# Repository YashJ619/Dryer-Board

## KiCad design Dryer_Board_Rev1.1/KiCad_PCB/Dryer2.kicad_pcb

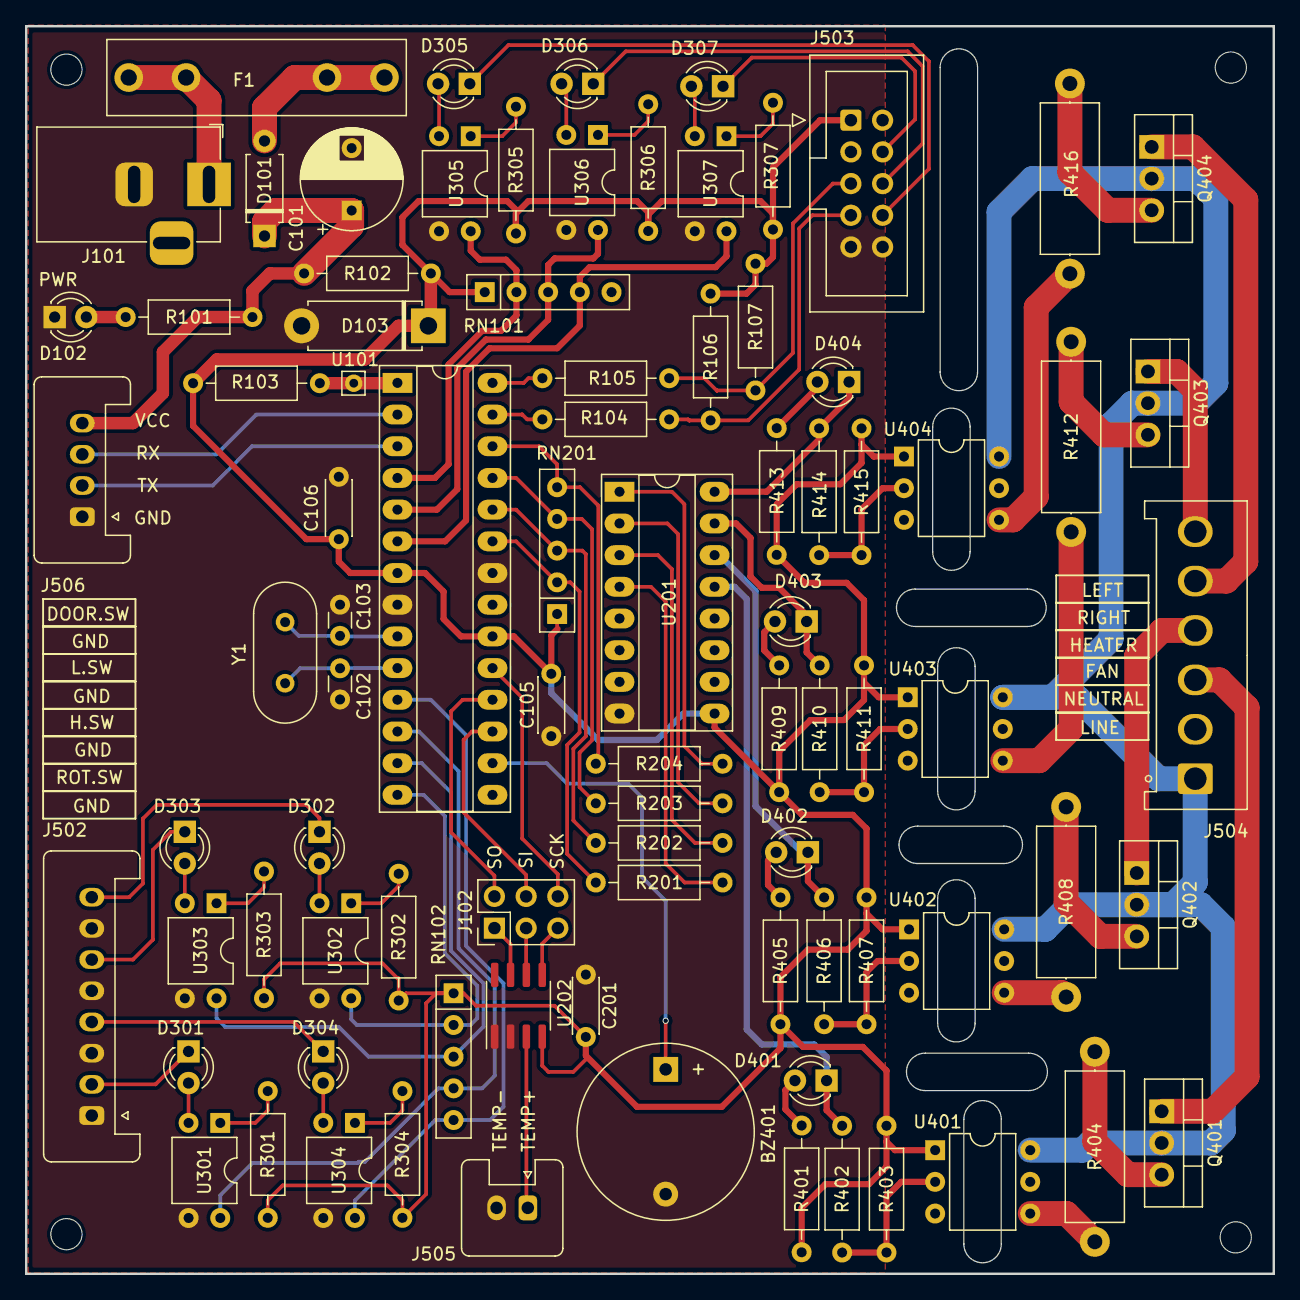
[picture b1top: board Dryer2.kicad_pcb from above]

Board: 2 copper layers, 100.0 x 100.0 mm, 89 parts (0 on the bottom side), 84 nets.

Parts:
BZ401: Buzzer; Buzzer_D14mm_H7mm_P10mm
C101: 220uF16v; CP_Radial_D8.0mm_P5.00mm
C102, C103: 22p; C_Disc_D3.0mm_W1.6mm_P2.50mm
C105, C106, C201: 100n; C_Disc_D4.3mm_W1.9mm_P5.00mm
D101: 1N5819; D_A-405_P7.62mm_Horizontal
D102, D301, D302, D303, D304, D305, D306, D307, D401, D402, D403, D404: LED; LED_D3.0mm
D103: 5.1v; D_5W_P10.16mm_Horizontal
F1: 1A; Fuseholder_Littelfuse_100_series_5x20mm
H501: 2.5MM; MountingHole_2.5mm
H502, H503, H504: MountingHole; MountingHole_2.5mm
J101: DC_Jack; BarrelJack_Horizontal
J102: MAX_AVR_SPI; PinHeader_2x03_P2.54mm_Vertical
J502: INPUT; Stocko_MKS_1658-6-0-808_1x8_P2.50mm_Vertical
J503: PANEL; IDC-Header_2x05_P2.54mm_Vertical
J504: MOTOR; Hirose_DF63-6P-3.96DSA_1x06_P3.96mm_Vertical
J505: Thermocupler; Stocko_MKS_1652-6-0-202_1x2_P2.50mm_Vertical
J506: UART; Stocko_MKS_1654-6-0-404_1x4_P2.50mm_Vertical
Q401, Q402, Q403, Q404: BTA16-800B; TO-220-3_Vertical
R101, R103, R201, R202, R203, R204, R401, R403, R405, R407, R409, R411, R413, R415: 1k; R_Axial_DIN0207_L6.3mm_D2.5mm_P10.16mm_Horizontal
R102: 4R7; R_Axial_DIN0207_L6.3mm_D2.5mm_P10.16mm_Horizontal
R104, R105: 22R; R_Axial_DIN0207_L6.3mm_D2.5mm_P10.16mm_Horizontal
R106, R107: 10K; R_Axial_DIN0207_L6.3mm_D2.5mm_P10.16mm_Horizontal
R301, R302, R303, R304, R305, R306, R307: 470R; R_Axial_DIN0207_L6.3mm_D2.5mm_P10.16mm_Horizontal
R402, R406, R410, R414: 150R; R_Axial_DIN0207_L6.3mm_D2.5mm_P10.16mm_Horizontal
R404, R408, R412, R416: 1.5K; R_Axial_DIN0414_L11.9mm_D4.5mm_P15.24mm_Horizontal
RN101, RN102, RN201: 10K; R_Array_SIP5
U101: ATmega328P-P; DIP-28_W7.62mm_Socket_LongPads
U201: ULN2003A; DIP-16_W7.62mm_Socket_LongPads
U202: MAX6675; SOIC-8_3.9x4.9mm_P1.27mm
U301, U302, U303, U304, U305, U306, U307: PC817; DIP-4_W7.62mm
U401, U402, U403, U404: MOC3041M; DIP-6_W7.62mm
Y1: 16MHz; Crystal_HC18-U_Vertical

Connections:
#DRUM_LEFT: D401.1 (K), R402.1, U201.13 (O4)
#DRUM_RIGHT: D402.1 (K), R406.1, U201.14 (O3)
#FAN: D404.1 (K), R414.1, U201.16 (O1)
#HEATER: D403.1 (K), R410.1, U201.15 (O2)
#RESET: R103.2, U101.1 (~RESET/PC6)
+5V: C105.1, C106.1, C201.2, D103.1 (K), J503.1, R102.1, R103.1, R106.1, R107.1, R301.1, R302.1, R303.1, R304.1, R305.1, R306.1, R307.1, R401.2, R403.1, R405.2, R407.1, R409.2, R411.1, R413.2, R415.1, RN101.1 (common), RN102.1 (common), RN201.1 (common), U101.7 (VCC), U101.20 (AVCC), U201.9 (COM), U202.4 (VCC), U401.1, U402.1, U403.1, U404.1
/MCU/AVR_SCL: R105.1, U101.28 (PC5)
/MCU/AVR_SDA: R104.1, U101.27 (PC4)
/MCU/XTAL+: C102.2, U101.10 (XTAL2/PB7), Y1.2
/MCU/XTAL-: C103.1, U101.9 (XTAL1/PB6), Y1.1
/ULN2003 MAX6675/D_FAN: R204.2, U201.1 (I1)
/ULN2003 MAX6675/D_HEATER: R203.2, U201.2 (I2)
/ULN2003 MAX6675/D_LEFT: R201.2, U201.4 (I4)
/ULN2003 MAX6675/D_RIGHT: R202.2, U201.3 (I3)
AVR_SCK: J102.6, U101.19 (PB5)
AVR_SI: J102.4, U101.17 (PB3)
AVR_SO: J102.2, U101.18 (PB4)
BUZZER: BZ401.1 (-), U101.16 (PB2)
DOOR_SW: RN102.4 (R3), U101.12 (PD6), U301.4
DOOR_SW_IN: D301.1 (K), J502.2
DRUM_LEFT: R201.1, RN201.2 (R1), U101.23 (PC0)
DRUM_LEFT_LINE: J504.3, Q401.1 (A1)
DRUM_RIGHT: R202.1, RN201.3 (R2), U101.24 (PC1)
DRUM_RIGHT_LINE: J504.4, Q402.1 (A1)
FAN: R204.1, RN201.5 (R4), U101.26 (PC3)
FAN_LINE: J504.5, Q404.1 (A1)
GND: BZ401.2 (+), C101.2, C102.1, C103.2, C105.2, C106.2, C201.1, D102.1 (K), D103.2 (A), J101.2, J502.1, J502.3, J502.5, J502.7, J503.9, J503.10, J505.2, J506.1, U101.8 (GND), U101.22 (AGND), U201.8 (GND), U202.1 (GND), U202.2 (T-), U301.3, U302.3, U303.3, U304.3, U305.3, U306.3, U307.3
HEATER: R203.1, RN201.4 (R3), U101.25 (PC2)
HEATER_LINE: J504.6, Q403.1 (A1)
HEATER_SW: RN102.3 (R2), U101.13 (PD7), U303.4
HEATER_SW_IN: D303.1 (K), J502.6
HIGH_KEY_SW: RN101.4 (R3), U101.6 (PD4), U307.4
HIGH_KEY_SW_IN: D307.1 (K), J503.4
LIMIT_SW: RN102.2 (R1), U101.14 (PB0), U302.4
LIMIT_SW_IN: D302.1 (K), J502.8
LINE_IN: J504.1, Q401.2 (A2), Q402.2 (A2), Q403.2 (A2), Q404.2 (A2), U401.6, U402.6, U403.6, U404.6
LOW_KEY_SW: RN101.2 (R1), U101.4 (PD2), U305.4
LOW_KEY_SW_IN: D305.1 (K), J503.8
MED_KEY_SW: RN101.3 (R2), U101.5 (PD3), U306.4
MED_KEY_SW_IN: D306.1 (K), J503.6
unnamed: D101.2 (A), F1.2
unnamed: D102.2 (A), R101.1
unnamed: D301.2 (A), U301.2
unnamed: D302.2 (A), U302.2
unnamed: D303.2 (A), U303.2
unnamed: D304.2 (A), U304.2
unnamed: D305.2 (A), U305.2
unnamed: D306.2 (A), U306.2
unnamed: D307.2 (A), U307.2
unnamed: D401.2 (A), R401.1
unnamed: D402.2 (A), R405.1
unnamed: D403.2 (A), R409.1
unnamed: D404.2 (A), R413.1
unnamed: F1.1, J101.1
unnamed: Q401.3 (G), R404.2
unnamed: Q402.3 (G), R408.2
unnamed: Q403.3 (G), R412.2
unnamed: Q404.3 (G), R416.2
unnamed: R301.2, U301.1
unnamed: R302.2, U302.1
unnamed: R303.2, U303.1
unnamed: R304.2, U304.1
unnamed: R305.2, U305.1
unnamed: R306.2, U306.1
unnamed: R307.2, U307.1
unnamed: R402.2, R403.2, U401.2
unnamed: R404.1, U401.4
unnamed: R406.2, R407.2, U402.2
unnamed: R408.1, U402.4
unnamed: R410.2, R411.2, U403.2
unnamed: R412.1, U403.4
unnamed: R414.2, R415.2, U404.2
unnamed: R416.1, U404.4
RX: J506.3, U101.2 (PD0)
SCL: J503.5, R105.2, R107.2
SDA: J503.7, R104.2, R106.2
SEL_ROT_SW: RN102.5 (R4), U101.11 (PD5), U304.4
SEL_ROT_SW_IN: D304.1 (K), J502.4
TEMP+: J505.1, U202.3 (T+)
TX: J506.2, U101.3 (PD1)
T_CS: J102.3, U202.6 (~CS)
T_SCK: J102.5, U202.5 (SCK)
T_SO: J102.1, U202.7 (SO)
VCC: C101.1, D101.1 (K), J506.4, R101.2, R102.2

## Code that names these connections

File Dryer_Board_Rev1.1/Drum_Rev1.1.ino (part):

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#include <max6675.h>
#include <LiquidCrystal_I2C.h>

#define DRUM_LEFT_PIN   A0
#define DRUM_RIGHT_PIN  A1
#define FAN_PIN         A2
#define HEATER_PIN      A3

#define SELECT_ROTATION_PIN    8
#define DOOR_PIN               5
#define LIMIT_SW_PIN           6
#define HEATERTEMP_SW_PIN      7

#define LOW_SET_PIN     2
#define MED_SET_PIN     3
#define HIGH_SET_PIN    4

#define BUZZER_PIN      10

#define TEMP_PIN_S0        11
#define TEMP_PIN_CS        12
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void setup() {
  Serial.begin(9600);

  pinMode(DRUM_LEFT_PIN, OUTPUT);
  pinMode(DRUM_RIGHT_PIN, OUTPUT);
  pinMode(FAN_PIN, OUTPUT);
  pinMode(HEATER_PIN, OUTPUT);

  pinMode(BUZZER_PIN, OUTPUT);

  pinMode(DOOR_PIN, INPUT_PULLUP);
  pinMode(HEATERTEMP_SW_PIN, INPUT_PULLUP);
  pinMode(LIMIT_SW_PIN, INPUT_PULLUP);
  pinMode(SELECT_ROTATION_PIN, INPUT_PULLUP);

  pinMode(LOW_SET_PIN, INPUT_PULLUP);
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      if (heatCountdownTime == 0)
      {
        gap = 3;
        digitalWrite(HEATER_PIN, LOW);
      }
    }
    else if (coolCountdownTime > 0)
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    {
      processcomplete = true;
      buzzer = !buzzer;
      digitalWrite(BUZZER_PIN, buzzer);
    }
    else
    {
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    else {
      heatererror = false;
    }
    if (digitalRead(LIMIT_SW_PIN)) {
      limitswerror = true;
    }
    else {
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{
  stopdrum();
  stopbuzzer();
  digitalWrite(FAN_PIN, LOW);
  digitalWrite(HEATER_PIN, LOW);
}

void stopbuzzer()
{
  buzzer = false;
  digitalWrite(BUZZER_PIN, buzzer);
}
void stopdrum()
{
  digitalWrite(DRUM_LEFT_PIN, LOW);
  digitalWrite(DRUM_RIGHT_PIN, LOW);
}

void drumstartwithheater(uint32_t htime)
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    //Serial.println(drumTemp);
    if ((drumTemp < (setTemp - 5)) && (drumTemp > 0))                //Turn heater ON if current temperature is less than (set temperature - 2)
    {
      digitalWrite(HEATER_PIN, HIGH);
    }
    else if ((drumTemp > (setTemp + 2)) || (drumTemp <= 0))       //Turn heater OFF if current temperature is more than (set temperature + 5)
    {
      digitalWrite(HEATER_PIN, LOW);
    }
    else;
  }
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{
  if (Time > 0)
  {
    digitalWrite(FAN_PIN, HIGH);
    if (anticlockwise && gap == 0)
    {
      digitalWrite(DRUM_LEFT_PIN, HIGH);
      digitalWrite(DRUM_RIGHT_PIN, LOW);
    }
    else if (clockwise && gap == 0)
    {
      digitalWrite(DRUM_LEFT_PIN, LOW);
      digitalWrite(DRUM_RIGHT_PIN, HIGH);
    }
    else {
      stopdrum();
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
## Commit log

2022-11-19 Adding Version Control to this project. Added Board and Code from clint side for optimization.
2022-11-19 Dryer Board Rev1.1 files added.
2022-11-20 Break-out code for Display and keyboard added
